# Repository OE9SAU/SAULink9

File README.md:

# SAULink9 - DIY interface for your analog radio

SAULink9 is a DIY project that bridges analog radios with the SVXLink Austria network or any other SVXLink networks like FM-FUNKNETZ.
It’s designed for amateur radio operators who want to flexibly connect their analog repeaters or other analog devices.

## NEWS
neue Scipts verfügbar!

## Highlights

🔹 Base system: cost-effective Raspberry Pi 3B+

🔹 Wide-range power input (9–24 VDC) via integrated DC-DC converter

🔹[Front panel](https://github.com/OE9SAU/SAULink9/tree/main/Node_Case)
 * Start/Shutdown button
 * Status LEDs for system monitoring
 * Easy SD card front access for quick updates and maintenance
   
🔹 All key connections located on the [Back panel](https://github.com/OE9SAU/SAULink9/tree/main/Node_Case) for neat cabling
 * DC-In
 * TRX connection
 * 1-Wire temperature sensor to monitor TRX temperature
 * USB
 * Network

🔹 [PiHat for Rpi3B+](https://github.com/OE9SAU/SAULink9/tree/main/Rpi_Hat)
  * front panel connection point
  * Convenient access to 4 GPIOs (for relays or other circuits)
  * FET-controlled fan output
  * Dedicated 1-Wire port
  * External voltage detection via optocoupler
  * Extra DIY prototyping space

🔹[ATPI USB-Soundinterface with CM108](https://github.com/OE9SAU/SAULink9/tree/main/ATPI)
    
🔹 Compatible with mostly any analog TRX devices

🔹 DIY & flexible – easy to set up and adapt to your needs

🔹 Direct connection to the [SVXLink Austria Reflektor OE9XFP](http://oe9xvi.dyndns.org:46197)

🔹 Built-in EchoLink integration

🔹 Works seamlessly with other SVXLink networks such as FM-FUNKNETZ

🔹 Open source & community-driven – can be further developed together

#### SAULink9 extends the range and flexibility of your analog radios and makes getting started with the SVXLink project particularly easy.

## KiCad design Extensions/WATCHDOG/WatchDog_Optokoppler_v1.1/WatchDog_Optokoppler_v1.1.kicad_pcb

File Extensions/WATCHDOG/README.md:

## SAULink9 Watchdog v1.1

The watchdog timer is repeatedly started by a trigger. If the trigger is missing, the timer with 33sec runs down and then the output switch to ...

v1.1: Add R7 & R8 to define PULLUP or PULLDOWN, without R7 & R8 acting potentialfree

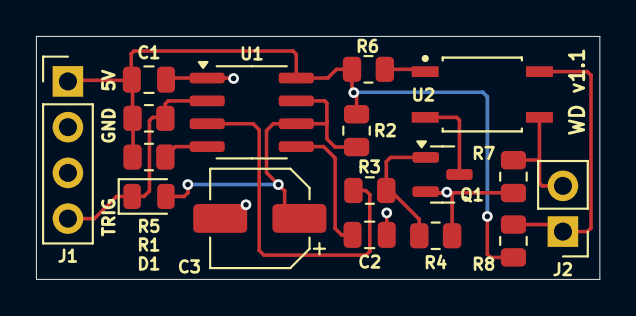
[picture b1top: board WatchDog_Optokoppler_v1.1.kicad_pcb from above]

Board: 2 copper layers, 31.3 x 13.5 mm, 17 parts (0 on the bottom side), 12 nets.

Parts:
C1: 100nF; C_0805_2012Metric
C2: 10nF; C_0805_2012Metric
C3: 100uF/16V; CP_Elec_5x5.9
D1: 1N4148; D_0805_2012Metric
J1: Conn_01x04_Pin; PinHeader_1x04_P2.54mm_Vertical
J2: REMOTE-CONTACT; PinHeader_1x02_P2.54mm_Vertical
Q1: AO3400A; SOT-23
R1, R5, R7, R8: 10k; R_0805_2012Metric
R2: 270K; R_0805_2012Metric
R3: 100R; R_0805_2012Metric
R4: 100k; R_0805_2012Metric
R6: 680R; R_0805_2012Metric
U1: NE555D; SOIC-8_3.9x4.9mm_P1.27mm
U2: EL357N-G; OPTO_EL357N-G

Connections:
GND: C1.1, C2.1, C3.2, J1.2, Q1.2 (S), R4.1, R7.1, U1.1 (GND)
unnamed: C3.1, D1.2 (A), R2.2, U1.6 (THR), U1.7 (DIS)
unnamed: D1.1 (K), J1.4, R5.1, U1.2 (TR)
unnamed: C1.2, J1.1, R1.1, R2.1, R5.2, R6.2, R8.2, U1.8 (VCC)
unnamed: J2.1, R8.1, U2.4
unnamed: J2.2, R7.2, U2.3
unnamed: Q1.3 (D), U2.2
unnamed: Q1.1 (G), R3.2, R4.2
unnamed: R6.1, U2.1
unnamed: C2.2, U1.5 (CV)
unnamed: R3.1, U1.3 (Q)
unnamed: R1.2, U1.4 (R)

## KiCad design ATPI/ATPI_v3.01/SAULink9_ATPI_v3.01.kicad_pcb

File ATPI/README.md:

# SAULink9 ATPI

This project based on a CM108 soundchip provides an Audio and PTT (Push-to-Talk) interface to connect your analog radio.
Mainly it acts as a bridge between SAULink9 nodes and external radio hardware for any SVXLink network or any other applications.

### Features:

* Audio input/output

  * 100K potentiometer enables you to make fine tuned adjustments to the audio going in to the CM108 (GM340 etc)
    
  * Output audio levels are generally set in whichever software you're using with the ATPI

* PTT line control to GND thru optocoupler

* COS (Carrier on Squelch) input blocked by diode

* Easy integration/replacement into existing SAULink9 / SVXLink setups

* Customizing the device name with integrated EEPROM

* works with VARA

### Versions
v3.0: like v2.0 with EEPROM for Device name informations

v2.0: shorter version without 1:1 transformer

v1.1: like v1.0 footprint D1 changed to SOD-123

v1.0: with 1:1 transformer -> Audio level to low

### Note
all versions must be ordered in 1.2mm PCB thickness

all versions must be glued together with the empty board version, ordered as well with 1.2mm PCB thicknes, to achieve the USB connector thickness of around 2.5mm

v3.0

v2.0

v1.1

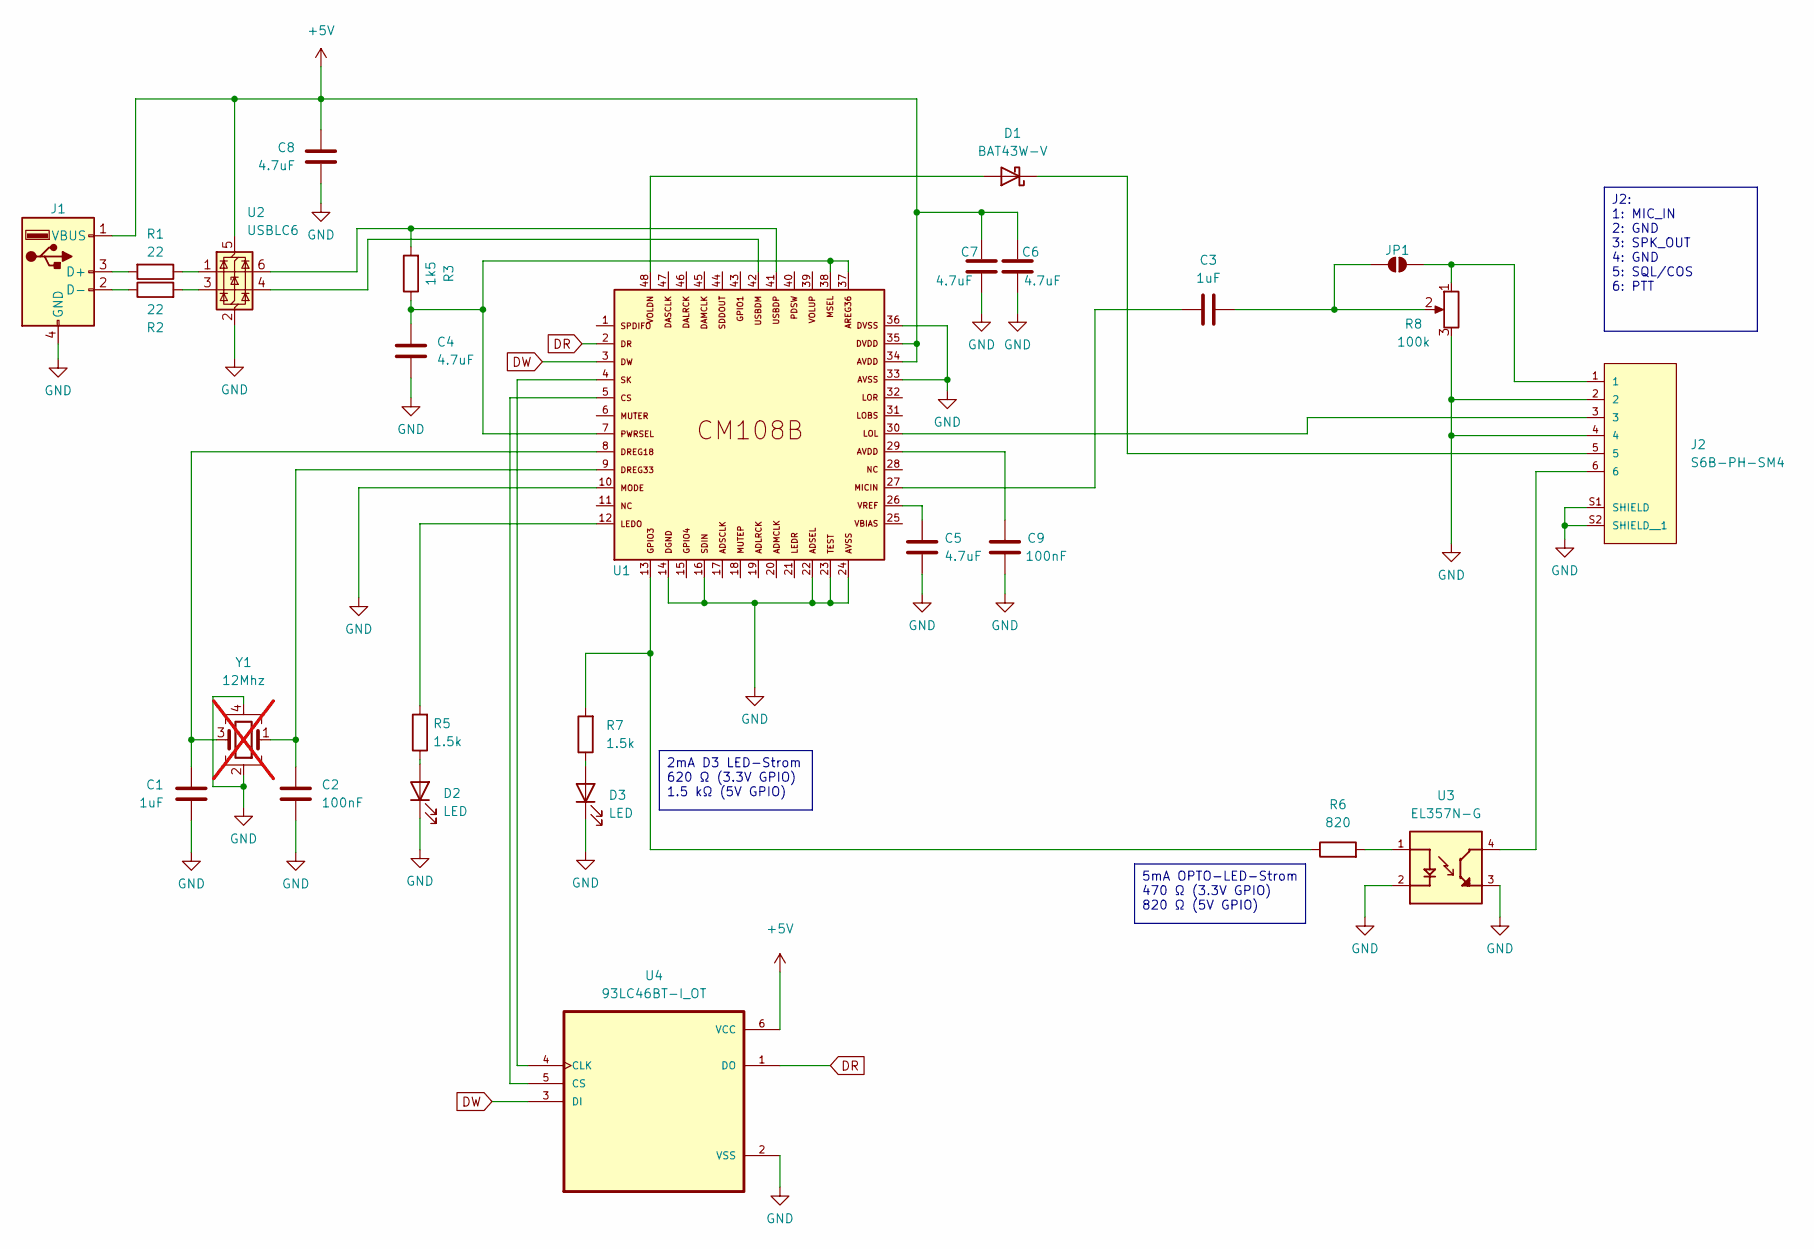
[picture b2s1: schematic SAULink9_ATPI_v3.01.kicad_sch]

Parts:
C1: 1uF; C_0805_2012Metric_Pad1.18x1.45mm_HandSolder
C2: 100nF; C_0805_2012Metric_Pad1.18x1.45mm_HandSolder
C3: 1uF; C_0805_2012Metric
C4, C5, C6, C7, C8: 4.7uF; C_0805_2012Metric
C9: 100nF; C_0805_2012Metric
D1: BAT43W-V; D_SOD-123
D2, D3: LED; LED_0805_2012Metric
J1: USB_A_PCB_Edge_receptacle
J2: S6B-PH-SM4; JST_S6B-PH-SM4-TB_LF__SN_
JP1: SolderJumper_2_Open
R1, R2: 22; R_0805_2012Metric
R3: 1k5; R_0805_2012Metric
R5, R7: 1.5k; R_0805_2012Metric
R6: 820; R_0805_2012Metric
R8: 100k; Potentiometer_Bourns_TC33X_Vertical
U1: CM108B; TQFP48
U2: USBLC6; SOT-23-6
U3: EL357N-G; OPTO_EL357N-G; PARTREV 6
U4: 93LC46BT-I_OT; SOT-23-6
Y1: 12Mhz; Crystal_SMD_3225-4Pin_3.2x2.5mm; not fitted

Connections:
+5V: C6.1, C7.1, C8.1, J1.1 (VBUS), U1.34, U1.35, U2.5 (VBUS), U4.6 (VCC)
DR: U1.2, U4.1 (DO)
DW: U1.3, U4.3 (DI)
GND: C1.1, C2.2, C4.2, C5.2, C6.2, C7.2, C8.2, C9.2, D2.1 (K), D3.1 (K), J1.4 (GND), J2.2, J2.4, J2.S1 (SHIELD), J2.S2 (SHIELD__1), R8.3, U1.10, U1.14, U1.16, U1.22, U1.23, U1.24, U1.33, U1.36, U2.2 (GND), U3.2, U3.3, U4.2 (VSS), Y1.2, Y1.4
unnamed: C1.2, U1.8, Y1.3
unnamed: C2.1, U1.9, Y1.1
unnamed: C3.1, U1.27
unnamed: C4.1, R3.1, U1.7, U1.37, U1.38
unnamed: C5.1, U1.26
unnamed: C9.1, U1.29
unnamed: D1.2 (A), U1.48
unnamed: D1.1 (K), J2.5
unnamed: D2.2 (A), R5.1
unnamed: D3.2 (A), R7.1
unnamed: J1.3 (D+), R1.2
unnamed: J1.2 (D-), R2.1
unnamed: J2.3, U1.30
unnamed: J2.6, U3.4
unnamed: C3.2, JP1.1 (A), R8.2
unnamed: J2.1, JP1.2 (B), R8.1
unnamed: R1.1, U2.1 (I/O1)
unnamed: R2.2, U2.3 (I/O2)
unnamed: R3.2, U1.41, U2.6 (I/O1)
unnamed: R5.2, U1.12
unnamed: R6.1, R7.2, U1.13
unnamed: R6.2, U3.1
unnamed: U1.42, U2.4 (I/O2)
unnamed: U1.4, U4.4 (CLK)
unnamed: U1.5, U4.5 (CS)

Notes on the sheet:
2mA D3 LED-Strom 620 Ω (3.3V GPIO) 1.5 kΩ (5V GPIO)
5mA OPTO-LED-Strom 470 Ω (3.3V GPIO) 820 Ω (5V GPIO)
J2: 1: MIC_IN 2: GND 3: SPK_OUT 4: GND 5: SQL/COS 6: PTT

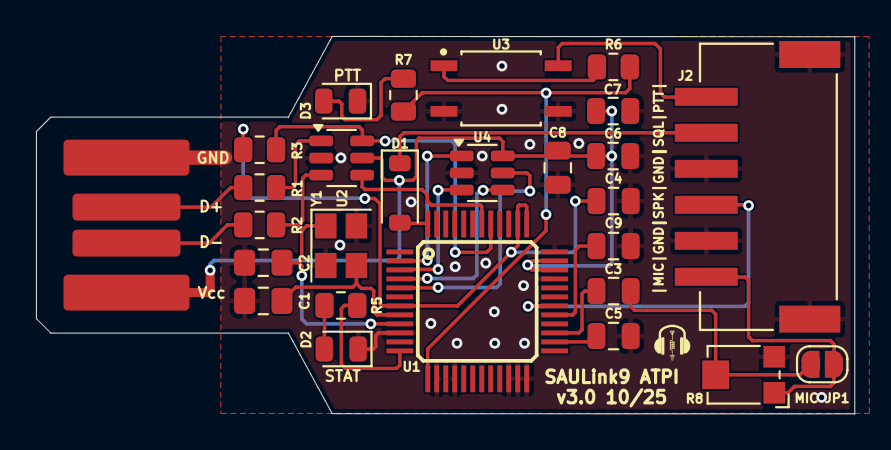
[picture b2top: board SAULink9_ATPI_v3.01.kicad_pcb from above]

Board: 2 copper layers, 45.5 x 21.0 mm, 28 parts (0 on the bottom side), 29 nets.

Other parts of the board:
G10: LOGO

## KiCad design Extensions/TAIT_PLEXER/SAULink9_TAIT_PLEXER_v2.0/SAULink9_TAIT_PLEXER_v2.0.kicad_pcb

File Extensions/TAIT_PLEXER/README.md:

## SAULink9 TAIT-PLEXER

In case of problems like no reflector connection or SAULink9 down, SAULink9 Watchdog (Extensions/WATCHDOG) sets the TAIT-PLEXER 

to LOW and both TAIT device are acting as local fm-repeater

v1.0 Testdesign

v1.1 changed pinout v1.0 by handwiring for current TAIT pinout config

v2.0 changed pinout for current TAIT pinout config

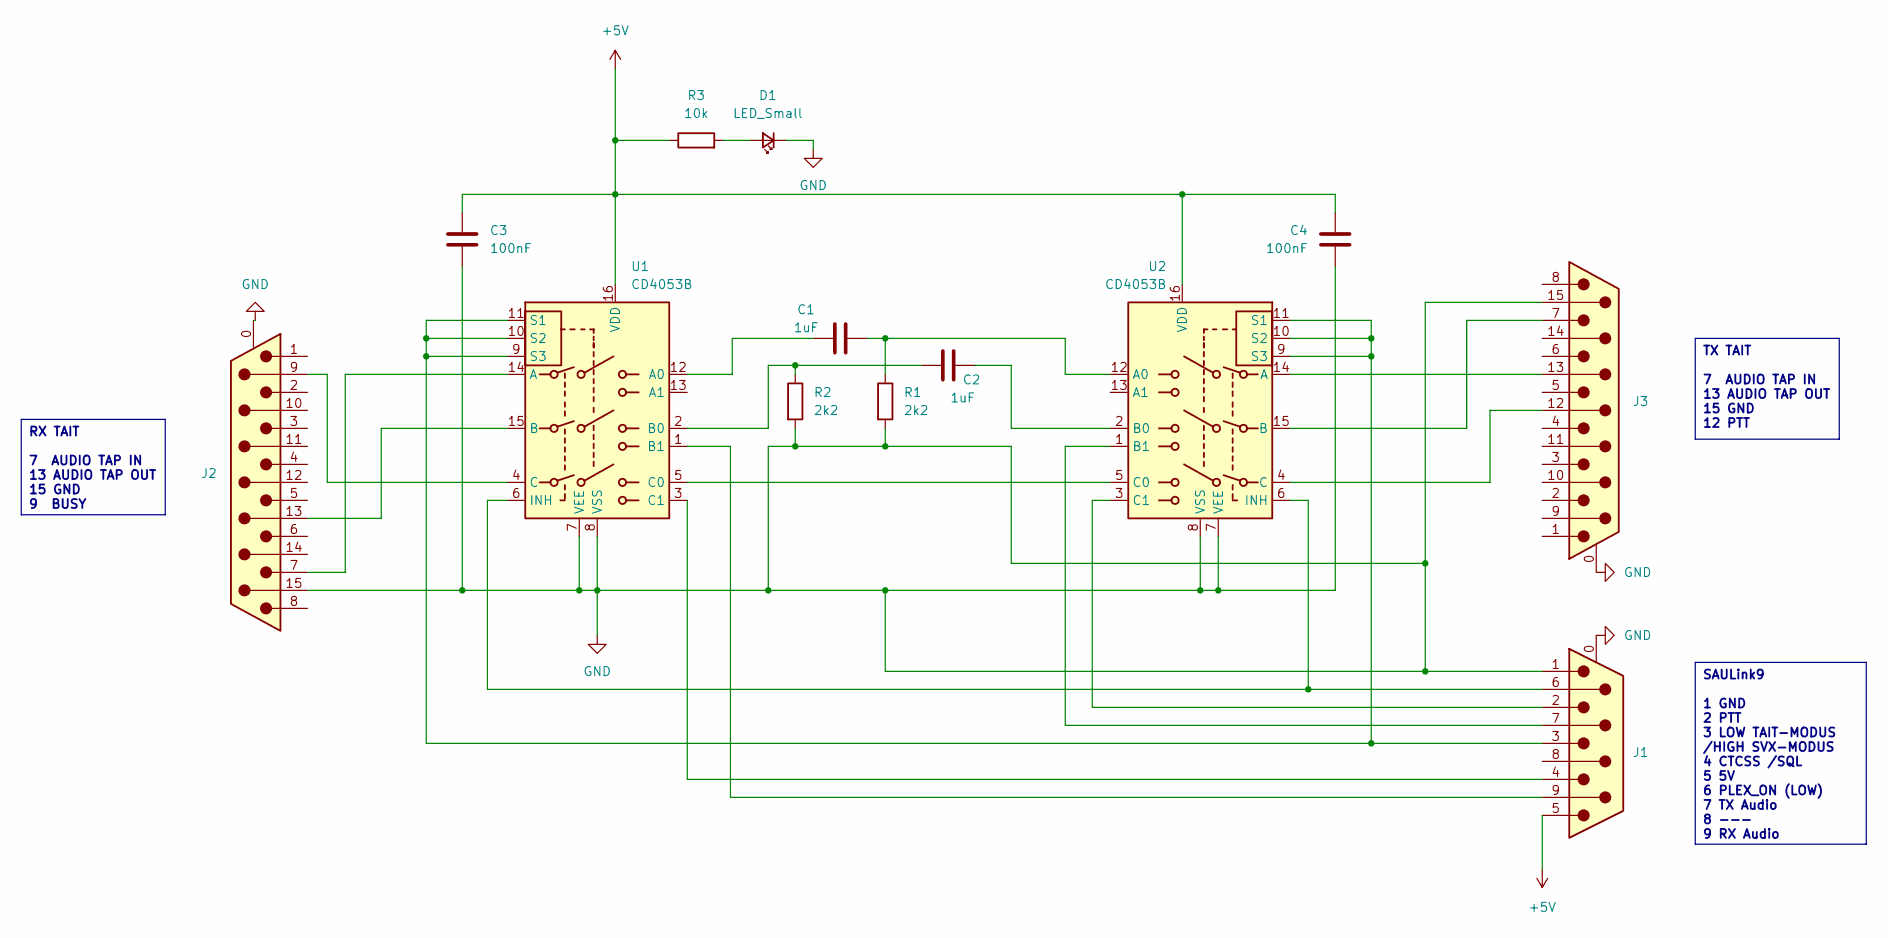
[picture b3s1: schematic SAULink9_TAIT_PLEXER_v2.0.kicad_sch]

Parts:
C1, C2: 1uF; C_0805_2012Metric
C3, C4: 100nF; C_0805_2012Metric
D1: LED_Small; LED_0805_2012Metric
J1: DE9_Pins; DSUB-9_Socket_Horizontal_P2.77x2.84mm_EdgePinOffset7.70mm_H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
J2, J3: DA15_Pins_MountingHoles; DSUB-15_Socket_Horizontal_P2.77x2.84mm_EdgePinOffset7.70mm_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
R1, R2: 2k2; R_0805_2012Metric
R3: 10k; R_0805_2012Metric
U1, U2: CD4053B; SOP-16_4.55x10.3mm_P1.27mm

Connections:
+5V: C3.1, C4.1, J1.5, R3.1, U1.16 (VDD), U2.16 (VDD)
GND: C3.2, C4.2, D1.1 (K), J1.0 (PAD), J1.1, J2.0 (PAD), J2.15, J3.0 (PAD), J3.15, R1.2, R2.2, U1.7 (VEE), U1.8 (VSS), U2.7 (VEE), U2.8 (VSS)
unnamed: D1.2 (A), R3.2
unnamed: J2.9, U1.4 (C)
unnamed: J2.13, U1.15 (B)
unnamed: J3.12, U2.4 (C)
unnamed: J3.13, U2.14 (A)
unnamed: C1.1, U1.12 (A0)
unnamed: J2.7, U1.14 (A)
unnamed: C2.1, R2.1, U1.2 (B0)
unnamed: J1.9, U1.1 (B1)
unnamed: U1.5 (C0), U2.5 (C0)
unnamed: J1.4, U1.3 (C1)
unnamed: J1.6, U1.6 (INH), U2.6 (INH)
unnamed: J1.3, U1.9 (S3), U1.10 (S2), U1.11 (S1), U2.9 (S3), U2.10 (S2), U2.11 (S1)
unnamed: C1.2, R1.1, U2.12 (A0)
unnamed: C2.2, U2.2 (B0)
unnamed: J1.7, U2.1 (B1)
unnamed: J3.7, U2.15 (B)
unnamed: J1.2, U2.3 (C1)

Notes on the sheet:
SAULink9 1 GND 2 PTT 3 LOW TAIT-MODUS /HIGH SVX-MODUS 4 CTCSS /SQL 5 5V 6 PLEX_ON (LOW) 7 TX Audio 8 --- 9 RX Audio
RX TAIT 7 AUDIO TAP IN 13 AUDIO TAP OUT 15 GND 9 BUSY
TX TAIT 7 AUDIO TAP IN 13 AUDIO TAP OUT 15 GND 12 PTT

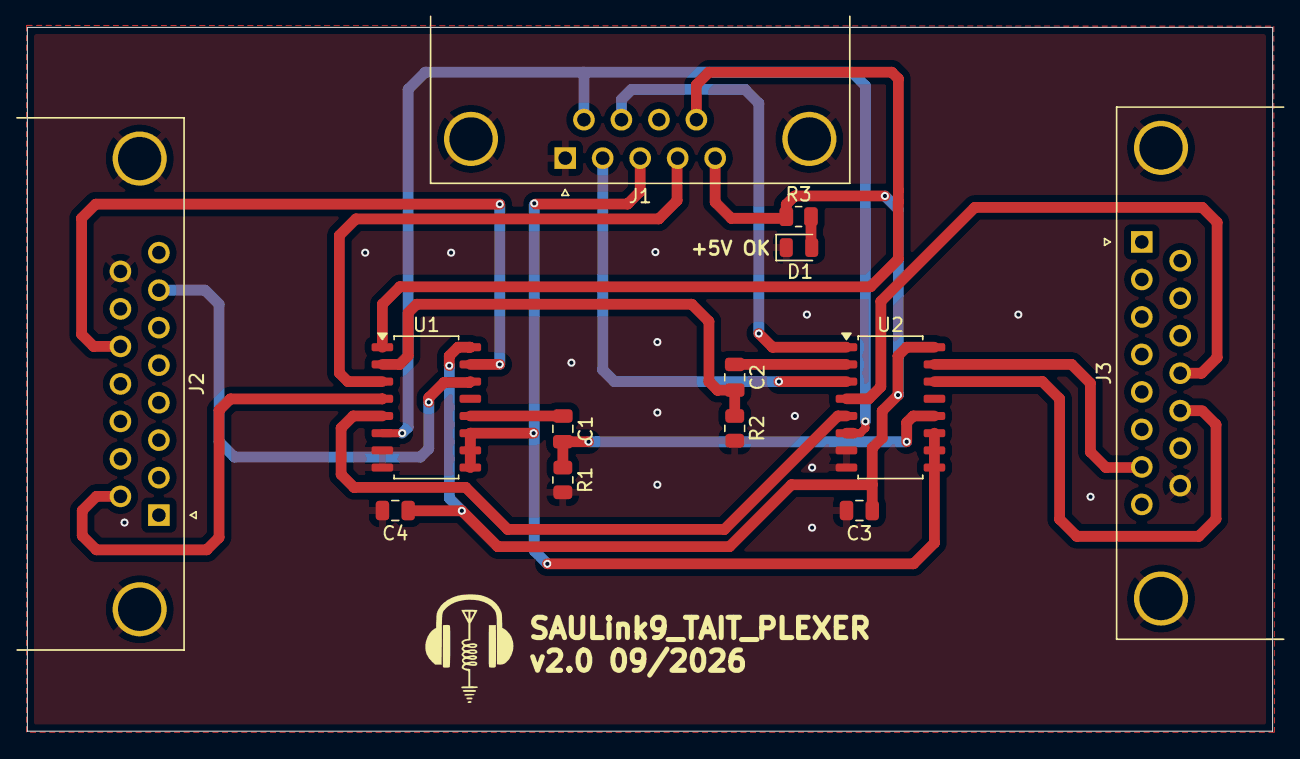
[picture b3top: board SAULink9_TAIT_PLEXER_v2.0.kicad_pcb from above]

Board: 2 copper layers, 92.0 x 52.0 mm, 15 parts (1 on the bottom side), 20 nets.

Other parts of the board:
G1, G2: LOGO

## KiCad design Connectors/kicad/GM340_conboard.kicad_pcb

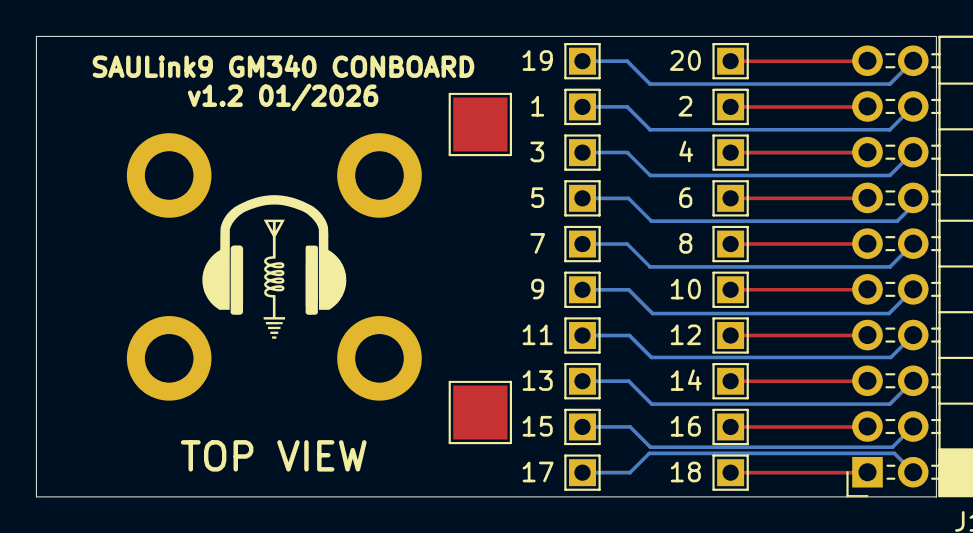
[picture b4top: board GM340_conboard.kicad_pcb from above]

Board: 2 copper layers, 50.0 x 25.6 mm, 27 parts (1 on the bottom side), 20 nets.

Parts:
1, 2, 3, 4, 5, 6, 7, 8, 9, 10, 11, 12, 13, 14, 15, 16, 17, 18, 19, 20: TestPoint; TestPoint_THTPad_1.5x1.5mm_Drill0.7mm
G1, G2: LOGO
J1: Conn_02x10_Top_Bottom; PinSocket_2x10_P2.54mm_Horizontal
REF1, REF2, REF3, REF4: MountingHole_2.7mm_M2.5_DIN965_Pad

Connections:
unnamed: 18.1, J1.1
unnamed: 17.1, J1.2
unnamed: 16.1, J1.3
unnamed: 15.1, J1.4
unnamed: 14.1, J1.5
unnamed: 13.1, J1.6
unnamed: 12.1, J1.7
unnamed: 11.1, J1.8
unnamed: 10.1, J1.9
unnamed: 9.1, J1.10
unnamed: 8.1, J1.11
unnamed: 7.1, J1.12
unnamed: 6.1, J1.13
unnamed: 5.1, J1.14
unnamed: 4.1, J1.15
unnamed: 3.1, J1.16
unnamed: 2.1, J1.17
unnamed: 1.1, J1.18
unnamed: 20.1, J1.19
unnamed: 19.1, J1.20

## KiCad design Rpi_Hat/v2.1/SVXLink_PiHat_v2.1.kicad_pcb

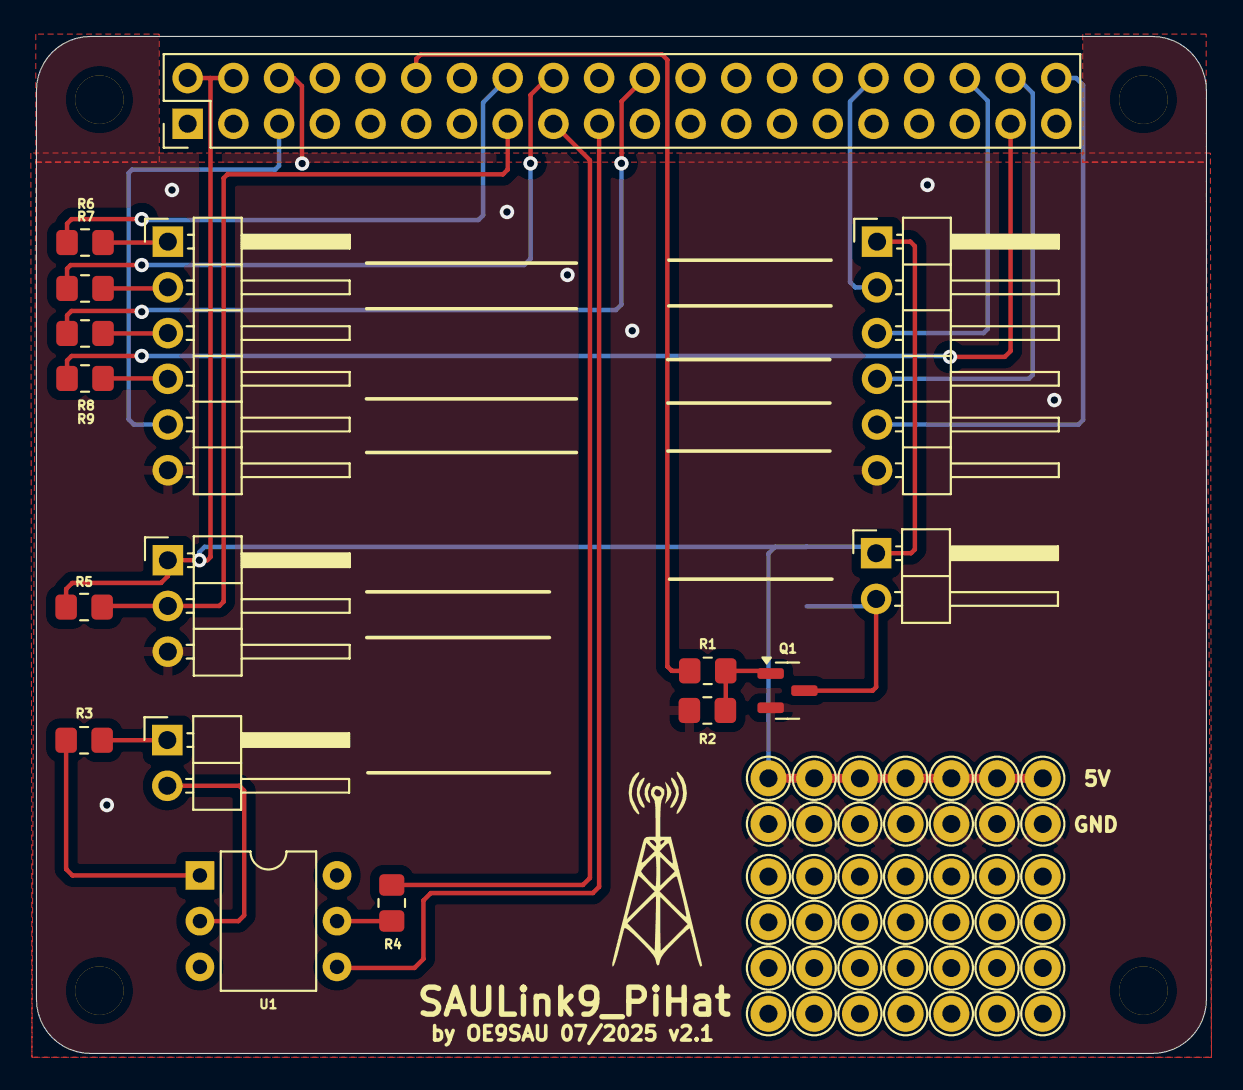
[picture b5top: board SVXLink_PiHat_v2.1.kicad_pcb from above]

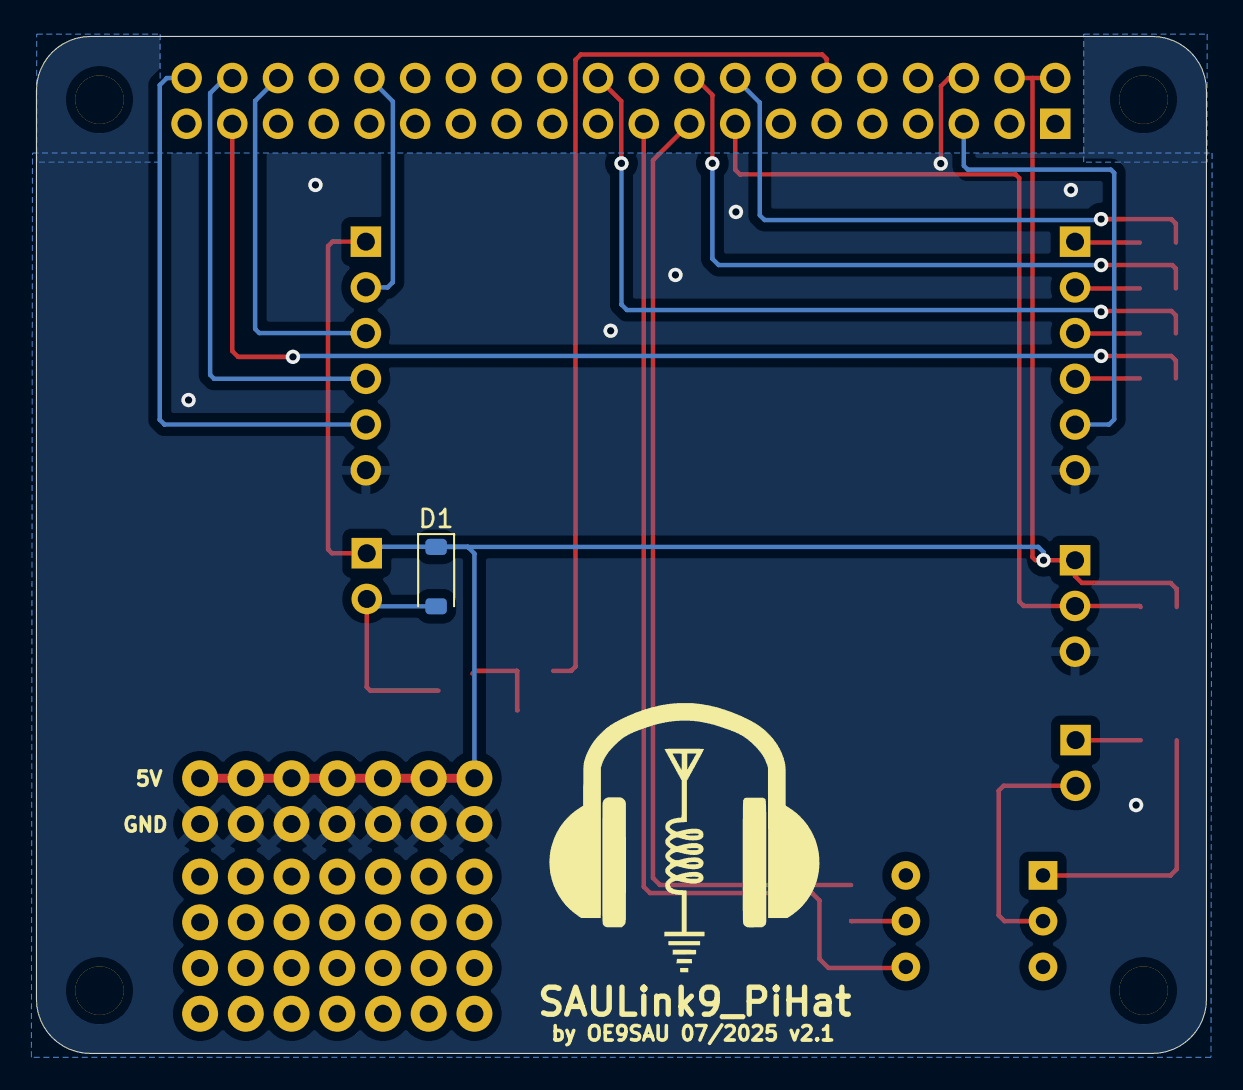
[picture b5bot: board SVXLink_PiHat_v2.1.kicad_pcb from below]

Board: 2 copper layers, 65.0 x 56.5 mm, 66 parts (2 on the bottom side), 25 nets.

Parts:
D1: 1N4148; D_SOD-123
G1: LOGO
G10: LOGO
J1: Raspberry_Pi_3; ESQ-120-14-T-D
J2: TRX; PinHeader_1x02_P2.54mm_Horizontal
J3: 1-Wire; PinHeader_1x03_P2.54mm_Horizontal
J4: FronPanel; PinHeader_1x06_P2.54mm_Horizontal
J4#2: RelayModule; PinHeader_1x06_P2.54mm_Horizontal
M1: Fan; PinHeader_1x02_P2.54mm_Horizontal
Q1: AO3400A; SOT-23
R1, R5: 470; R_0805_2012Metric_Pad1.20x1.40mm_HandSolder
R2: 100k; R_0805_2012Metric_Pad1.20x1.40mm_HandSolder
R3, R4: 1k; R_0805_2012Metric_Pad1.20x1.40mm_HandSolder
R6, R7, R8, R9: 0R; R_0805_2012Metric_Pad1.20x1.40mm_HandSolder
REF1, REF2, REF3, REF4: MountingHole_2.7mm_M2.5
TP1, TP2, TP3, TP4, TP5, TP6, TP7, TP8, TP9, TP10, TP11, TP12, TP13, TP14, TP15, TP16, TP17, TP18, TP19, TP20, TP21, TP22, TP23, TP24, TP25, TP26, TP27, TP28, TP29, TP30, TP31, TP31#2, TP32, TP33, TP34, TP35, TP35#2, TP36, TP37, TP321, TP333, TP341: TestPoint; TestPoint_THTPad_D2.0mm_Drill1.0mm
U1: 4N37; DIP-6_W7.62mm

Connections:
+3.3V: J1.1 (3V3), J1.17 (3V3), R4.2
+5V: D1.1 (K), J1.2 (5V), J1.4 (5V), J3.1, J4#2.1, M1.1 (+), R5.1, TP1.1, TP6.1, TP11.1, TP16.1, TP21.1, TP26.1, TP31#2.1
GND: J1.6 (GND), J3.3, J4.6, J4#2.6, Q1.2 (S), R2.2, TP2.1, TP7.1, TP12.1, TP17.1, TP22.1, TP27.1, TP321.1
GPIO3: J1.5 (SCL/GPIO3), J4.5
unnamed: D1.2 (A), M1.2 (-), Q1.3 (D)
unnamed: J1.36 (GPIO16), J4#2.3
unnamed: J1.12 (GPIO18/PWM0), R1.1
unnamed: J1.38 (GPIO20/MOSI1), J4#2.4
unnamed: J1.40 (GPIO21/SCLK1), J4#2.5
unnamed: J1.15 (GPIO22), J3.2, R5.2
unnamed: J1.16 (GPIO23), R6.2
unnamed: J1.18 (GPIO24), R7.2
unnamed: J1.22 (GPIO25), R8.2
unnamed: J1.37 (GPIO26), R9.2
unnamed: J1.19 (MOSI0/GPIO10), U1.4
unnamed: J1.32 (PWM0/GPIO12), J4#2.2
unnamed: J2.1, R3.1
unnamed: J2.2, U1.2
unnamed: J4.1, R6.1
unnamed: J4.2, R7.1
unnamed: J4.3, R8.1
unnamed: J4.4, R9.1
unnamed: Q1.1 (G), R1.2, R2.1
unnamed: R3.2, U1.1
unnamed: R4.1, U1.5

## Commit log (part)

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2025-09-25 Config-Files
2025-09-25 node_case_front
2025-09-25 png_correction
2025-09-26 add_partlist
2025-09-26 EEPROM_stuff
2025-09-27 Pihat_v2.1
2025-09-27 v2.1
2025-09-28 Utility
2025-09-29 File_Update
2025-09-29 CM108_EEPROM_Utility
2025-09-29 EEPROM_Util
2025-09-30 yaml_settings
2025-10-02 bom_adding
2025-10-06 yaml_update
2025-10-06 Readme
2025-10-06 File Update
2025-10-06 files update
2025-10-17 EEpromTool
2025-10-17 Code
2025-10-17 Tool
2025-10-17 FinalFiles
2025-10-17 Clarify configuration file reference in README
    Updated README to clarify configuration file usage.
2025-10-17 Clarify configuration programming instructions
    Updated usage instructions for programming configuration.
2025-11-14 Update README with links to front and back panels
2025-12-04 Upload conboard
2025-12-05 BasePlate_update
2025-12-05 Commits
2025-12-08 Inside_png
2025-12-23 Some PCB updates
2026-01-02 v1.1
2026-01-09 Update_Baseplate
2026-01-09 bom_update_vswr
2026-01-10 scripting
2026-01-10 script_update
2026-01-10 Readme Update
2026-01-10 Change name
2026-01-15 manual update
2026-01-18 new_conbaord
2026-01-18 pic_update
2026-01-24 Update image display method in README.md
    Replace image syntax with HTML for better alignment.
2026-01-27 Fix spelling and enhance description in README
    Corrected spelling of 'LED`s' to 'LEDs' and improved description.
2026-01-27 Update README with clarification on LED status display
2026-01-27 Modify installation command in README
    Updated installation instructions for svxlink-gpio-status.py.
2026-01-27 Fix command formatting in installation section
    Correct formatting of the installation command in the README.
2026-01-27 Update LED behavior description for 'UP' state
2026-01-27 Fix formatting in README for LED behavior table
2026-01-27 Refine README for update scripts
    Updated the README to improve clarity and consistency in the script descriptions.
2026-01-27 Update README to reflect new reflector connections
2026-01-27 Fix formatting in README for LED status display
2026-01-27 Modify service activation commands in README
    Updated commands for enabling the service to use '&&' for chaining.
2026-01-27 Update installation instructions for svxlink scripts
2026-01-27 Fix installation path for svxlink_service_led.py
    Updated installation instructions to reflect the correct file path for svxlink_service_led.py.
2026-01-27 Update service activation instructions in README
2026-01-27 Update service activation instructions in README
    Replaced svxlink-gpio-status.service with svxlink_service_led.service in the README.
2026-01-27 Revise installation and service commands in README
    Updated installation instructions and service management commands in README.
2026-01-27 Update installation instructions and service activation
2026-01-28 Simplify service activation commands in README
2026-01-28 Format service activation commands for readability
2026-02-05 upload_ap_extension
2026-02-28 Watchdog_update
2026-02-28 watchdog_upload
2026-02-28 file_upload
2026-02-28 kicad_files
2026-02-28 readme_updates
2026-02-28 pcb_update
2026-02-28 kicad_export
2026-02-28 file_move
2026-02-28 kicad-files
2026-03-03 service_led_update
2026-03-05 Tait-Plexer
2026-03-16 TAIT_CROSS_PCB
2026-03-16 GM340_con
2026-03-16 TAIT_PLEXER_UPD
2026-03-17 PCB_UPD
2026-03-29 Commit -ATPI-Tool
2026-03-29 Commit-ATPI-Tool
2026-03-30 ATPI_EEprom_Settings_Update
2026-04-02 WD_v1.1
2026-04-02 Commits_v1.1
2026-04-14 Step_Upload
2026-04-16 bom_commits
2026-05-08 Commits_Plexer_v2.0
2026-05-08 PCB_Commits
2026-05-12 gerber
2026-05-18 Commits_lh_php
2026-05-18 Remove file deletion from lh_update.sh
    Removed file deletion commands from the update script.
2026-05-18 lh_php commits
2026-05-21 Commits_lh
